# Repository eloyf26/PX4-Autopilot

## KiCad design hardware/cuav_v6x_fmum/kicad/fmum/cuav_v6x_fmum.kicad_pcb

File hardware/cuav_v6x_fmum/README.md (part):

# CUAV V6X FMUM — what the board is, and a reverse-engineered schematic

Two photos of a small green 36 × 31 mm board, silkscreened **`V6X_FMUM RC11`**, a
CUAV logo and the date code **07-17/23**. This folder identifies it, explains every
visible part, and reconstructs its schematic well enough to build a compatible
replica.

| File | What it is |
| --- | --- |
| `README.md` | this document |
| `kicad/fmum/cuav_v6x_fmum.kicad_pro` | **KiCad 8 project of the FMU module**: 4 schematic sheets + `cuav_v6x_fmum.kicad_pcb` (36 × 31.4 mm, 6 layers, placed, net-assigned, unrouted) |
| `kicad/imu/cuav_v6x_imu.kicad_pro` | **KiCad 8 project of the IMU board**: schematic + `cuav_v6x_imu.kicad_pcb` (~25 × 18 mm octagon, 4 layers, placed, unrouted) |
| `kicad/lib/` | the official KiCad 8 footprints used (fetched from the 8.0.8 library tag) and ST's pin-data XML for the STM32H743IIKx ball map |
| `parts.py` | the parts database: every component, its real package pin numbers and nets, board side and position |
| `gen_kicad.py`, `gen_pcb.py` | generators for the schematics and the two PCBs (run in this order) |
| `schematic/01…07_*.svg` | seven schematic sheets (MCU, core peripherals, power + sensors, X1, X2, IMU flex, IMU board) |
| `netlist.csv` | every MCU pin / connector pin / IMU-board pin → net → destination, machine readable |
| `gen_schematic.py` | the pin / connector tables the SVG sheets, netlist and `parts.py` are built from |
| `build_html.py` | generator for the HTML report |
| `cuav_v6x_fmum_schematic.html` | self-contained report (same content as the published artifact) |
| `photos/` | the four source photos (FMU module and IMU board), downscaled |

> **Are these the official schematics? No.** CUAV does not publish the schematic of
> the V6X modules, and the full Pixhawk FMUv6X reference schematics are available only
> to Dronecode Foundation members. Everything here is an independent reconstruction.
> Connectivity is derived from the firmware that runs on this exact hardware, so it is
> reliable; part choices for regulators and passives are engineering substitutes.

> **Provenance / confidence.** No vendor schematic of this module is public. The
> schematic below was rebuilt from three sources that describe this exact hardware:
> (1) the PX4 board support package the module runs
> (`boards/px4/fmu-v6x`, hardware type `V6X001` = "CUAV sensor set rev 1"), which
> hard-codes every MCU pin, bus, chip-select, address and power-enable;
> (2) the two public Pixhawk standards the module implements, DS-010 *Pixhawk
> Autopilot Bus* (the 100- and 50-pin connector pinouts) and DS-012 *Pixhawk
> Autopilot FMUv6X* (sensor sets, the 34-pin IMU flex pinout, mechanical drawing);
> (3) the photos, for placement, packages and markings.
> Pin-to-net connectivity is therefore high confidence. Passive values, regulator
> part numbers and a few small ICs are educated engineering choices and are
> marked as such.

---

## 1. Identification

**It is the FMU core module ("FMUM") of the CUAV Pixhawk V6X flight controller.**

The Pixhawk V6X is a modular autopilot: a *base board* (all the JST-GH connectors,
power selection, CAN/USB/Ethernet transceivers, the STM32F103 IO co-processor) and a
plug-in *FMU module* carrying the main processor, storage and part of the sensor set.
The two boards meet through the **Pixhawk Autopilot Bus (PAB)**: one 100-pin and one
50-pin Hirose DF40 connector with a 3 mm stack height. Your board is the plug-in
module. CUAV sells the V6X either complete or as this "core" alone (43 g, 36 × 31.4 mm
per the standard's mechanical drawing, which the photos match to the millimetre:
four 2.0 mm grounded mounting holes, R2.3 corners, LEDs and SD slot in the
standardised positions).

Everything on it maps to the standard's reference module drawing (DS-012 p.10,
"FMUv6X FMUM"): same FLEX connector position, same TRACE pad footprint, same
LED/SD/battery placement. CUAV re-laid the board but kept the reference architecture.

### What the photos show

**Photo 1 — MCU side (this is the *bottom* of the module; it faces the base board)**

| What you see | What it is | Confidence |
| --- | --- | --- |
| 10 × 10 mm BGA marked ARM / `STM32H7…IIK6` | **U1, STM32H743IIK6** (or H753, the crypto variant PX4 is configured for). Cortex-M7 at 480 MHz, 2 MB flash, 1 MB RAM, UFBGA176+25 package. | high |
| 100-pin fine-pitch connector, left | **X1** Hirose DF40C-100DP-0.4V — the main Pixhawk Autopilot Bus | high |
| 50-pin fine-pitch connector, right | **X2** Hirose DF40C-50DP-0.4V — Ethernet RMII + external SPI bus | high |
| 3 × 3 mm QFN, top centre | **ICM-20649** 6-axis IMU (#3), on SPI1 — the one "hard mounted" IMU of the set | high (from firmware; size matches QFN-24 3×3) |
| tiny metal-lidded part with a port hole, sitting in a U-shaped routed slot, top right | **ICP-20100** barometer (#2), on I2C2 at 0x63. The slot is stress relief: board flex would otherwise read as pressure. | high (2 × 2.5 mm metal-lid LGA is unique to a baro) |
| two small metal cans left of the MCU (`TW2…` rectangular, `A-T` square) | **Y1 16 MHz** HSE crystal (3225) and **Y2 32.768 kHz** RTC crystal | high (PX4 board.h: 16 MHz HSE, 32.768 kHz LSE) |
| small blue 1.5 mm part marked `IY2K`, right of the IMU | small passive/IC, probably an ESD/TVS array or a tiny LDO for the sensor domain | low |
| QFN + large inductor + capacitors, bottom centre | **U_REG**, the module's 5 V → 3.3 V step-down for `FMU_VDD_3V3` | medium |
| SOT-23-5 ICs and clusters of 0402 capacitors along the right edge | the four **switched sensor LDOs** (`VDD_3V3_SENSORS1…4`) with their decoupling | medium |
| `TP1` | test pad | — |
| ladders of 0402 resistors bottom right | hardware-ID resistor ladders + I²C pull-ups (1.5 kΩ, required on the module by DS-010) | medium |

**Photo 2 — SD-card side (the *top* of the module; visible when installed)**

| What you see | What it is | Confidence |
| --- | --- | --- |
| `CUAV`, `V6X_FMUM RC11`, `07-17/23`, arrow | vendor, board name (V6X **F**light **M**anagement **U**nit **M**odule), layout revision RC11, build date; the arrow is the flight direction reference for the IMUs | high |
| 34-pin connector labelled `FLEX`, left | **J3** Hirose BM20B(0.8)-34DP-0.4V, FPC to CUAV's separate, vibration-isolated **IMU board** (BMI088, ICM-42688-P, RM3100, ICP-20100 #1, calibration EEPROM). That is why the "triple-redundant IMU" is not visible here: two of the three IMUs and the compass live on the other board. | high |
| microSD push-push slot marked `molex 2011EC` | **J4** microSD, SDMMC2 4-bit, PX4 logs go here | high |
| SOIC-8, top centre | **FM25V02A** 256 kbit FRAM (SPI5) — PX4 parameter storage. FRAM is used instead of flash because it survives millions of writes and needs no erase. | high |
| 3 × 3 mm QFN marked `S50 08 07 AD307`, right of the SD slot | most likely **NXP SE050** secure element (I2C4, 0x48) — it is in the FMUv6X reference sensor set and PX4 defines its address for this board | medium |
| round metal can marked `L03`, bottom right | **B1**, RTC backup cell (rechargeable lithium coin/cylinder). Keeps the clock and backup SRAM alive without main power; exported to the base on X1-29. | high (role) / medium (exact part) |
| three 0603 LEDs bottom left | **D1 red, D2 green, D3 blue** status LEDs (PE3/PE4/PE5, active-low) | high |
| row of 8 pads + 2 large pads, bottom left | unpopulated **J1 TRACE** footprint (Cortex-M ETM trace: TRACECLK + TRACED0-3) | high |
| `BT0` pad | **BOOT0** — bridge to 3.3 V at power-up to enter the STM32 ROM (DFU) bootloader | high |
| `TP2 TP3 TP4 TP7` | test pads (nets unknown) | — |
| SOT-23 / 0603 parts around the right edge | the remaining sensor LDO and its decoupling, RTC charging diode + resistor | medium |

### Sensor set of this exact revision (from `boards/px4/fmu-v6x/init/rc.board_sensors`, branch `V6X001`)

| Sensor | Part | Bus | CS / address | DRDY | Power domain | Where |
| --- | --- | --- | --- | --- | --- | --- |
| IMU 1 | Bosch **BMI088** (accel + gyro) | SPI3 | PI4 (accel), PI8 (gyro) | PI7 (gyro INT3) | `VDD_3V3_SENSORS3` | IMU board via J3 |
| IMU 2 | TDK **ICM-42688-P** | SPI2 | PH5 | PA10 | `VDD_3V3_SENSORS2` | IMU board via J3 |
| IMU 3 | TDK **ICM-20649** | SPI1 | PI9 | PF2 | `VDD_3V3_SENSORS1` | **this module** |
| Compass | PNI **RM3100** | I2C4 | 0x20 | — | `VDD_3V3_SENSORS4` | IMU board via J3 |
| Baro 1 | TDK **ICP-20100** | I2C4 | 0x64 | — | `VDD_3V3_SENSORS4` | IMU board via J3 |
| Baro 2 | TDK **ICP-20100** | I2C2 | 0x63 | PG5 (optional) | `VDD_3V3_SENSORS2` | **this module** |
| Cal EEPROM | 24LC64 | I2C4 | 0x50 | — | `VDD_3V3_SENSORS4` | IMU board via J3 |
| Parameters | **FM25V02A** FRAM | SPI5 | PG7 | — | `FMU_VDD_3V3` | **this module** |
| Secure element | NXP **SE050** | I2C4 | 0x48 | — | `FMU_VDD_3V3` | **this module** (likely) |

### The second board: `V6X IMU RC10` (2022-09-20)

The octagonal board on the other end of the FLEX cable is CUAV's **IMU board**. It sits
in an elastomer isolation mount (the two half-round notches and the four M1-M4 ground
pads are the mount interface), which is why it is a separate PCB at all: the inertial
sensors ride on a damped mass, while the processor board is bolted rigidly to the base.
It contains no regulators; all its power arrives over the flex.

| What you see | What it is | Confidence |
| --- | --- | --- |
| rectangular LGA, top left, sensor side | **Bosch BMI088** accel + gyro (IMU 1, SPI3) | high (package 3 × 4.5 mm, firmware) |
| small 3-row-marked LGA below it | **TDK ICM-42688-P** (IMU 2, SPI2) | high |
| 4 × 4 mm QFN, centre right | **PNI MagI2C**, the RM3100 compass controller (I2C4, 0x20) | high |
| two flat black bars marked `PNI`, one horizontal one vertical | **PNI Sen-XY-f** sense coils for the X and Y magnetic axes (mounted at 90°) | high |
| black cube below the QFN | **PNI Sen-Z-f** coil, Z axis | high |
| metal lid with port hole, bottom left | **TDK ICP-20100** barometer #1 (I2C4, 0x64) | high |
| white arrow | flight-direction reference for the IMU axes | high |
| flex side: 34-pin 0.4 mm connector `FLEX` | mating half of the FMUM's J3 (BM20 series); an FPC jumper links the two | high |
| flex side: SOIC-8 | **24LC64** calibration EEPROM (I2C4, 0x50; PX4 `imu_eeprom`: cal data, MFT revision, ID) | high |
| flex side: four large resistors marked `4700` | **470 Ω heater resistors**, paralleled (117 Ω across 5 V ≈ 0.21 W) | high |
| flex side: SOT-23 marked `3400` next to a resistor silkscreen symbol | **N-MOSFET (AO3400 class)**, low-side switch for the heater, gate on the `HEATER` line | high |
| remaining 0402/0603 parts | decoupling, gate pull-down | — |

Sheet `07_imu_board.svg` (and KiCad sheet 5) draws it. Because the flex pinout is fixed by
the standard, the IMU board and the FMU module are individually replaceable; the
sensor rotations PX4 applies (`-R 4` BMI088, `-R 6` ICM-42688-P, `-R 14` ICM-20649) encode how
each chip is oriented relative to the arrow.

---

## 2. How the module works (architecture)

```
             base board                        ┃  FMU module (this board)                         ┃  IMU board (flex)
                                               ┃                                                   ┃
  power path selector ── VDD_5V_IN ────────────╋──► U_REG 3.3 V ──► FMU_VDD_3V3 ──► U1 STM32H7     ┃
  (2 bricks + USB)      X1-49/51/53/55         ┃      │                     ├──► FM25V02A FRAM (SPI5) ┃
                                               ┃      │                     ├──► SE050 (I2C4)        ┃
                                               ┃      │                     ├──► microSD (SDMMC2, switched by PC13)
                                               ┃      ├──► LDO1 (PI11) ──► ICM-20649  (SPI1)        ┃
                                               ┃      ├──► LDO2 (PF4)  ──► ICP-20100 #2 (I2C2) ─────╋──► ICM-42688-P (SPI2)
                                               ┃      ├──► LDO3 (PE7)  ────────────────────────────╋──► BMI088 (SPI3)
                                               ┃      └──► LDO4 (PG8)  ────────────────────────────╋──► RM3100, ICP-20100 #1, EEPROM (I2C4)
  UARTs, CAN, USB, PWM, I2C1-3, ADC, IDs ◄─────╋── X1 (100 pins) ── U1 GPIO/peripherals             ┃      HEATER (PB10) ◄── J3-30
  LAN8742A PHY (RMII), payload SPI6 ◄──────────╋── X2 (50 pins)                                    ┃
```

Key ideas worth understanding before you copy it:

* **One supply in, everything else generated locally.** Only `VDD_5V_IN` enters (four
  pins for current). A step-down makes `FMU_VDD_3V3` for the MCU and memories, and that
  rail is *exported* on X1-84/86 so the base can run its own small logic from it.
* **Four independent sensor power domains.** Each IMU/compass group has its own 3.3 V
  LDO with an MCU-controlled enable and a 1:2 resistor divider read by the ADC. PX4 can
  power-cycle a misbehaving sensor domain without touching the others and can detect a
  sagging rail. This is the "three redundancy domains" design of FMUv6X.
* **Separate buses per IMU.** SPI1, SPI2, SPI3 each carry exactly one IMU (plus a data-ready
  interrupt line), so a hung device cannot block the others. I2C4 is the internal
  sensor I²C (compass, baro 1, EEPROM, secure element). I2C1/2/3 go out to the base for
  GPS/compass pucks and power monitors; baro 2 rides on I2C2 locally.
* **Storage:** FRAM for parameters (byte-writable, non-volatile), microSD for logs, backup
  SRAM + RTC kept alive by B1.
* **Hardware identification without firmware changes.** At boot PG0 drives 3.3 V into two
  resistor ladders; ADC3 reads the divider voltages. PH4 reads the *module* ladder
  (24.9 k / 442 k → ID 1 → "CUAV sensor set rev 1"), PH3 reads the *base board* ladder via
  X1-27. PX4 then starts exactly the right drivers with the right axis rotations.
* **Everything analog-ish that touches the outside world stays on the base**: USB/CAN
  transceivers, RS-232-level shifters, PHY magnetics, power switching, ESD. Only 3.3 V
  logic crosses X1/X2. That is what makes the module small and reusable.

---

## 3. Schematic sheets

### KiCad — two projects, two PCBs

```
kicad/fmum/cuav_v6x_fmum.kicad_pro     FMU module   (schematic, 4 sheets + PCB)
kicad/imu/cuav_v6x_imu.kicad_pro       IMU board    (schematic + PCB)
```

Open either `.kicad_pro` in KiCad 8 or newer. Everything is self-contained: symbols are
embedded in the sheets and footprints in the boards, so no library setup is needed.

**What the PCBs contain, and how much to trust each part**

| Item | Status |
| --- | --- |
| FMUM outline 36.0 × 31.4 mm, R2.3 corners, four ∅2.0 grounded holes at 2.3 mm from the edges | from the Pixhawk DS-010 drawing — exact |
| X1 / X2 positions (4.1 and 33.0 mm from the left edge in the base-side view, centred 14.5 mm from the bottom edge), pin 1 at the bottom, odd pins on the left in that view | from DS-010 — exact position; pin-1 corner follows the drawing |
| LED positions (blue 6.70, green 8.30, red 9.85 mm from the left, 2.3 mm from the bottom) | from DS-010 — exact |
| Baro stress-relief slot, IMU flex connector, microSD, FRAM, crystals, RTC cell, regulators, passives | positions read off the photos, about ±0.5 mm |
| Every pad's net (670 pads on the FMUM, 171 on the IMU board) | from the firmware pin map and the datasheets — reliable |
| STM32H743IIK6 footprint: 201 balls on a 0.65 mm grid, ball names from ST's own pin data, 0.30 mm pads | exact |
| Footprints for SOIC-8, QFN-20/24, LGA-14, SOT-23/-223, 0402/0603/0805, crystals, LEDs, microSD | official KiCad 8 library files (`kicad/lib/`) |
| Generated footprints: DF40 100/50-pin, BM20 34-pin, BMI088 LGA-16, ICP-20100 LGA-10, MagI2C MLF-28, PNI coils, RTC cell, test/trace pads | pin order from the datasheets; pad **geometry approximated** — compare with the Hirose / PNI / Bosch / TDK drawings before ordering boards |
| IMU board outline (25 × 18 mm octagon, 4.8 / 4.0 mm chamfers, ∅3 mm notches, ∅2.2 holes) | estimated from the photos using the coils and connector as scale |
| Copper routing, inner-layer planes, vias | **not included** — a 6-layer BGA design cannot be recovered from photographs. The ratsnest is complete; route it yourself |

Substitute parts (the replica choice, not the original): U2 3.3 V regulator (an LDO in SOT-223
stands in for CUAV's switching regulator), U3–U6 sensor LDOs (TLV75533 pinout: IN, GND, EN, NC, OUT),
U7 microSD load switch (check the pinout of the part you buy), BT1 (Seiko MS621FE footprint).
U11 (SE050 secure element) is placed with its pads deliberately **unassigned** because its pinout
could not be verified; PX4 runs without it.

**Working with it**

* Pin numbers in the schematic symbols are the real package pins, so *Update PCB from Schematic*
  round-trips cleanly. Click a global label and press ` to highlight a net across sheets.
* Front side of the FMUM PCB = SD-card side; the MCU, bus connectors, IMU 3 and barometer sit on the
  back (B.Cu), which is what plugs toward the base board.
* Set the FMUM stackup to 6 layers (F.Cu, In1–In4, B.Cu are defined); use In1/In4 as ground and
  power planes next to the outer layers, 0.1 mm/0.1 mm rules and 0.2 mm vias for the BGA escape.
* ERC/DRC will flag the intentionally open pins (X2 spares, SE050, unused INT pins) and the
  unrouted nets.
* Regenerate after editing `parts.py`: `python3 gen_kicad.py && python3 gen_pcb.py`.

### SVG sheets

Open the SVGs in `schematic/` (any browser or Inkscape). Net labels
follow the Pixhawk standard names so they line up with the published base-board
examples.

| Sheet | Content |
| --- | --- |
| `01_mcu_u1.svg` | U1 with every used pin: peripheral function inside, net outside, destination in the margin |
| `02_core_peripherals.svg` | FRAM, SE050, microSD + load switch, crystals, RTC cell, LEDs, USB, HW-ID ladder, BOOT0/NRST/TRACE |
| `03_power_and_sensors.svg` | 3.3 V step-down, four sensor LDOs with dividers, ICM-20649, ICP-20100 #2, heater line, I²C pull-ups |
| `04_x1_pab_100pin.svg` | X1 pin-by-pin with the MCU pin on each signal |
| `05_x2_pab_50pin.svg` | X2 pin-by-pin (RMII, SPI6, spares) |
| `06_j3_imu_flex_34pin.svg` | J3 IMU flex pin-by-pin |
| `07_imu_board.svg` | the IMU board: BMI088, ICM-42688-P, RM3100 (MagI2C + 3 coils), ICP-20100 #1, 24LC64, heater |

### Full MCU pin map (as used by PX4 on this module)

Column "goes to" uses the same vocabulary as the sheets: `X1-nn`, `X2-nn`, `J3-nn`, or an on-module part.

| Pin | Function | Net | Goes to |
| --- | --- | --- | --- |
| PA0 | ADC1_INP16 | SCALED_VDD_3V3_SENSORS1 | divider on sensor rail 1 |
| PA1 | ETH_REF_CLK | ETH_REF_CLK | X2-3 |
| PA2 | ETH_MDIO | ETH_MDIO | X2-2 |
| PA3 | USART2_RX | USART2_RX_TELEM3 | X1-42 |
| PA4 | ADC12_INP18 | SCALED_VDD_3V3_SENSORS2 | divider on sensor rail 2 |
| PA5 | SPI1_SCK | SPI1_SCK_SENSOR1 | ICM-20649 SCLK |
| PA6 | SPI6_MISO | SPI6_MISO_EXTERNAL1 | X2-31 |
| PA7 | ETH_CRS_DV | ETH_CRS_DV | X2-7 |
| PA8 | I2C3_SCL | I2C3_SCL_BASE | X1-10 |
| PA9 | OTG_FS_VBUS | VBUS_SENSE | X1-80 |
| PA10 | GPIO/EXTI | SPI2_DRDY2_IMU2_INT2 | J3-31 |
| PA11 | OTG_FS_DM | USB_D_N | X1-78 |
| PA12 | OTG_FS_DP | USB_D_P | X1-76 |
| PA13 | SWDIO | FMU_SWDIO | X1-75 |
| PA14 | SWCLK | FMU_SWCLK | X1-77 |
| PA15 | GPIO | SPI6_nCS2_EXTERNAL1 | X2-43 |
| PB0 | ADC12_INP9 | SCALED_VDD_3V3_SENSORS3 | divider on sensor rail 3 |
| PB1 | ADC12_INP5 | SCALED_V5 | divider on VDD_5V_IN |
| PB2 | SPI3_MOSI | SPI3_MOSI_SENSOR3 | J3-14 |
| PB3 | SPI6_SCK / SWO | SPI6_SCK_EXTERNAL1 | X2-35 |
| PB4 | SDMMC2_D3 | SD_D3 | microSD |
| PB5 | SPI1_MOSI | SPI1_MOSI_SENSOR1 | ICM-20649 SDI |
| PB6 | USART1_TX | USART1_TX_GPS1 | X1-36 |
| PB7 | USART1_RX | USART1_RX_GPS1 | X1-34 |
| PB8 | I2C1_SCL | I2C1_SCL_BASE | X1-18 |
| PB9 | I2C1_SDA | I2C1_SDA_BASE | X1-16 |
| PB10 | GPIO (TIM2_CH3) | HEATER | J3-30 |
| PB11 | ETH_TX_EN | ETH_TX_EN | X2-27 |
| PB12 | FDCAN2_RX | CAN2_RX | X1-59 |
| PB13 | FDCAN2_TX | CAN2_TX | X1-57 |
| PB14 | SDMMC2_D0 | SD_D0 | microSD |
| PB15 | SDMMC2_D1 | SD_D1 | microSD |
| PC0 | GPIO/EXTI | NFC_GPIO | X2-48 |
| PC1 | ETH_MDC | ETH_MDC | X2-4 |
| PC2 | ADC3_INP12 | ADC1_6V6 | X1-90 |
| PC3 | ADC3_INP13 | ADC1_3V3 | X1-92 |
| PC4 | ETH_RXD0 | ETH_RXD0 | X2-11 |
| PC5 | ETH_RXD1 | ETH_RXD1 | X2-15 |
| PC6 | USART6_TX | USART6_TX_TO_IO | X1-72 |
| PC7 | USART6_RX | USART6_RX_FROM_IO_RC | X1-70 |
| PC8 | UART5_RTS | UART5_RTS_TELEM2 | X1-58 |
| PC9 | UART5_CTS | UART5_CTS_TELEM2 | X1-60 |
| PC10 | SPI3_SCK | SPI3_SCK_SENSOR3 | J3-10 |
| PC11 | SPI3_MISO | SPI3_MISO_SENSOR3 | J3-12 |
| PC12 | UART5_TX | UART5_TX_TELEM2 | X1-52 |
| PC13 | GPIO | VDD_3V3_SD_CARD_EN | SD load switch |
| PC14/PC15 | OSC32 | 32 kHz crystal | Y2 |
| PD0 | FDCAN1_RX | CAN1_RX | X1-65 |
| PD1 | FDCAN1_TX | CAN1_TX | X1-63 |
| PD2 | UART5_RX | UART5_RX_TELEM2 | X1-54 |
| PD3 | USART2_CTS | USART2_CTS_TELEM3 | X1-48 |
| PD4 | USART2_RTS | USART2_RTS_TELEM3 | X1-46 |
| PD5 | USART2_TX | USART2_TX_TELEM3 | X1-40 |
| PD6 | SDMMC2_CK | SD_CLK | microSD |
| PD7 | SDMMC2_CMD | SD_CMD | microSD |
| PD8 | USART3_TX | USART3_TX_DEBUG | X1-69 |
| PD9 | USART3_RX | USART3_RX_DEBUG | X1-71 |
| PD10 | GPIO | FMU_nSAFETY_SWITCH_LED_OUT | X1-23 |
| PD11 | GPIO | SPI6_DRDY1_EXTERNAL1 | X2-47 |
| PD12 | GPIO | SPI6_DRDY2_EXTERNAL1 | X2-45 |
| PD13 | TIM4_CH2 | FMU_CH5 | X1-7 |
| PD14 | TIM4_CH3 | FMU_CH6 | X1-5 |
| PD15 | GPIO | spare | n.c. |
| PE0 | UART8_RX | UART8_RX_GPS2 | X1-30 |
| PE1 | UART8_TX | UART8_TX_GPS2 | X1-28 |
| PE2 | TRACECLK | TRACECLK | J1 pad 1 |
| PE3 | GPIO, open drain | nLED_RED | D1 (+ J1 pad 3) |
| PE4 | GPIO, open drain | nLED_GREEN | D2 (+ J1 pad 5) |
| PE5 | GPIO, open drain | nLED_BLUE | D3 (+ J1 pad 7) |
| PE6 | GPIO | nARMED | X1-85 (+ J1 pad 8) |
| PE7 | GPIO | VDD_3V3_SENSORS3_EN | LDO3 EN |
| PE8 | UART7_TX | UART7_TX_TELEM1 | X1-64 |
| PE9 | GPIO | SPIX_SYNC | X2-49 |
| PE10 | UART7_CTS | UART7_CTS_TELEM1 | X1-24 |
| PE11 | TIM1_CH2 capture | FMU_CAP1 | X1-97 |
| PE15 | GPIO | VDD_5V_PERIPH_nOC | X1-37 |
| PF0 | I2C2_SDA | I2C2_SDA_BASE | X1-12 + ICP-20100 #2 |
| PF1 | I2C2_SCL | I2C2_SCL_BASE | X1-14 + ICP-20100 #2 |
| PF2 | GPIO/EXTI | SPI1_DRDY1_IMU3_INT1 | ICM-20649 INT1 |
| PF4 | GPIO | VDD_3V3_SENSORS2_EN | LDO2 EN |
| PF5 | GPIO, pull-up | FMU_SAFETY_SWITCH_IN | X1-21 |
| PF6 | UART7_RX | UART7_RX_TELEM1 | X1-66 |
| PF7 | SPI5_SCK | SPI5_SCK_FRAM | FRAM SCK |
| PF8 | UART7_RTS | UART7_RTS_TELEM1 | X1-22 |
| PF9 | TIM14_CH1 | BUZZER_1 | X1-4 |
| PF10 | GPIO | SPI6_nRESET_EXTERNAL1 | X2-39 |
| PF11 | SPI5_MOSI | SPI5_MOSI_FRAM | FRAM SI |
| PF12 | ADC1_INP6 | SCALED_VDD_3V3_SENSORS4 | divider on sensor rail 4 |
| PF13 | GPIO | VDD_5V_HIPOWER_nOC | X1-83 |
| PF14 | I2C4_SCL | I2C4_SCL_FMU | J3-7 + SE050 |
| PF15 | I2C4_SDA | I2C4_SDA_FMU | J3-5 + SE050 |
| PG0 | GPIO | HW_VER_REV_DRIVE | X1-25 + module ID ladder |
| PG1 | GPIO, pull-up | nPOWER_IN_A | X1-89 |
| PG2 | GPIO, pull-up | nPOWER_IN_B | X1-91 |
| PG3 | GPIO, pull-up | nPOWER_IN_C | X1-93 |
| PG4 | GPIO | VDD_5V_PERIPH_nEN | X1-35 |
| PG5 | GPIO/EXTI | I2C2_DRDY1_BARO2 | ICP-20100 #2 INT (optional) |
| PG6 | GPIO, pull-up | PG6 | X2-44 |
| PG7 | GPIO | SPI5_nCS1_FRAM | FRAM nCS |
| PG8 | GPIO | VDD_3V3_SENSORS4_EN | LDO4 EN |
| PG9 | SPI1_MISO | SPI1_MISO_SENSOR1 | ICM-20649 SDO |
| PG10 | GPIO | VDD_5V_HIPOWER_nEN | X1-81 |
| PG11 | SDMMC2_D2 | SD_D2 | microSD |
| PG12 | ETH_TXD1 | ETH_TXD1 | X2-23 |
| PG13 | ETH_TXD0 | ETH_TXD0 | X2-19 |
| PG14 | SPI6_MOSI | SPI6_MOSI_EXTERNAL1 | X2-33 |
| PG15 | GPIO | ETH_POWER_EN | X2-6 |
| PH0/PH1 | OSC | 16 MHz crystal | Y1 |
| PH2 | GPIO | VDD_3V3_SPEKTRUM_POWER_EN | X1-33 |
| PH3 | ADC3_INP14 | HW_VER_SENSE | X1-27 (base ID ladder) |
| PH4 | ADC3_INP15 | HW_REV_SENSE | module ID ladder |
| PH5 | GPIO | SPI2_nCS1_IMU2 | J3-33 |
| PH6 | TIM12_CH1 | FMU_CH7 | X1-3 |
| PH7 | SPI5_MISO | SPI5_MISO_FRAM | FRAM SO |
| PH8 | I2C3_SDA | I2C3_SDA_BASE | X1-8 |
| PH9 | TIM12_CH2 | FMU_CH8 | X1-1 |
| PH10 | TIM5_CH1 | FMU_CH4 | X1-11 |
| PH11 | TIM5_CH2 | FMU_CH3 | X1-13 (+ X2-50) |
| PH12 | TIM5_CH3 | FMU_CH2 | X1-15 |
| PH13 | UART4_TX | UART4_TX | X1-98 |
| PH14 | UART4_RX | UART4_RX | X1-96 |
| PI0 | TIM5_CH4 | FMU_CH1 | X1-17 |
| PI1 | SPI2_SCK | SPI2_SCK_SENSOR2 | J3-20 |
| PI2 | SPI2_MISO | SPI2_MISO_SENSOR2 | J3-22 |
| PI3 | SPI2_MOSI | SPI2_MOSI_SENSOR2 | J3-24 |
| PI4 | GPIO | SPI3_nCS1_BMI088_ACCEL | J3-2 |
| PI5 | TIM8_CH1 capture | FMU_PPM_INPUT | X1-39 |
| PI6 | GPIO | SPI3_DRDY1_BMI088_INT1 | n.c. (not on flex) |
| PI7 | GPIO/EXTI | SPI3_DRDY2_BMI088_INT3_GYRO | J3-3 |
| PI8 | GPIO | SPI3_nCS2_BMI088_GYRO | J3-4 |
| PI9 | GPIO | SPI1_nCS1_IMU3 | ICM-20649 nCS |
| PI10 | GPIO | SPI6_nCS1_EXTERNAL1 | X2-41 |
| PI11 | GPIO | VDD_3V3_SENSORS1_EN | LDO1 EN |
| NRST | reset | FMU_nRST | X1-87 |
| BOOT0 | boot | BOOT0 | BT0 pad, 10 k to GND |
| VBAT | backup | V_RTC_BAT | B1 + X1-29 |

Serial ports as PX4 names them: USART1 = GPS1, USART2 = TELEM3, USART3 = debug
console, UART4 = "UART4/I2C3" port, UART5 = TELEM2, USART6 = PX4IO link and RC input
(1.5 Mbit/s), UART7 = TELEM1, UART8 = GPS2.

### X1 — 100-pin Pixhawk Autopilot Bus (module part: Hirose DF40C-100DP-0.4V(51))

Odd pins on one row, even on the other. `GND` pins: 2 6 9 19 20 26 31 32 38 41 43 44 45 47 50 56 61 62 67 68 73 74 79 82 88 94 95 99 100.

| Pin | Net | Pin | Net |
| --- | --- | --- | --- |
| 1 | FMU_CH8 (PH9) | 4 | BUZZER_1 (PF9) |
| 3 | FMU_CH7 (PH6) | 8 | I2C3_SDA (PH8) |
| 5 | FMU_CH6 (PD14) | 10 | I2C3_SCL (PA8) |
| 7 | FMU_CH5 (PD13) | 12 | I2C2_SDA (PF0) |
| 11 | FMU_CH4 (PH10) | 14 | I2C2_SCL (PF1) |
| 13 | FMU_CH3 (PH11) | 16 | I2C1_SDA (PB9) |
| 15 | FMU_CH2 (PH12) | 18 | I2C1_SCL (PB8) |
| 17 | FMU_CH1 (PI0) | 22 | UART7_RTS_TELEM1 (PF8) |
| 21 | FMU_SAFETY_SWITCH_IN (PF5) | 24 | UART7_CTS_TELEM1 (PE10) |
| 23 | FMU_nSAFETY_SWITCH_LED_OUT (PD10) | 28 | UART8_TX_GPS2 (PE1) |
| 25 | HW_VER_REV_DRIVE (PG0) | 30 | UART8_RX_GPS2 (PE0) |
| 27 | HW_VER_SENSE (PH3) | 34 | USART1_RX_GPS1 (PB7) |
| 29 | V_RTC_BAT (VBAT, B1) | 36 | USART1_TX_GPS1 (PB6) |
| 33 | VDD_3V3_SPEKTRUM_POWER_EN (PH2) | 40 | USART2_TX_TELEM3 (PD5) |
| 35 | VDD_5V_PERIPH_nEN (PG4) | 42 | USART2_RX_TELEM3 (PA3) |
| 37 | VDD_5V_PERIPH_nOC (PE15) | 46 | USART2_RTS_TELEM3 (PD4) |
| 39 | FMU_PPM_INPUT (PI5) | 48 | USART2_CTS_TELEM3 (PD3) |
| 49 51 53 55 | **VDD_5V_IN** (supply in) | 52 | UART5_TX_TELEM2 (PC12) |
| 57 | CAN2_TX (PB13) | 54 | UART5_RX_TELEM2 (PD2) |
| 59 | CAN2_RX (PB12) | 58 | UART5_RTS_TELEM2 (PC8) |
| 63 | CAN1_TX (PD1) | 60 | UART5_CTS_TELEM2 (PC9) |
| 65 | CAN1_RX (PD0) | 64 | UART7_TX_TELEM1 (PE8) |
| 69 | USART3_TX_DEBUG (PD8) | 66 | UART7_RX_TELEM1 (PF6) |
| 71 | USART3_RX_DEBUG (PD9) | 70 | USART6_RX_FROM_IO / RC (PC7) |
| 75 | FMU_SWDIO (PA13) | 72 | USART6_TX_TO_IO (PC6) |
| 77 | FMU_SWCLK (PA14) | 76 | USB_D_P (PA12) |
| 81 | VDD_5V_HIPOWER_nEN (PG10) | 78 | USB_D_N (PA11) |
| 83 | VDD_5V_HIPOWER_nOC (PF13) | 80 | VBUS_SENSE (PA9) |
| 85 | nARMED (PE6) | 84, 86 | **FMU_VDD_3V3** (3.3 V out) |
| 87 | FMU_nRST (NRST) | 90 | ADC1_6V6 (PC2) |
| 89 | nPOWER_IN_A (PG1) | 92 | ADC1_3V3 (PC3) |
| 91 | nPOWER_IN_B (PG2) | 96 | UART4_RX (PH14) |
| 93 | nPOWER_IN_C (PG3) | 98 | UART4_TX (PH13) |
| 97 | FMU_CAP1 (PE11) | | |

### X2 — 50-pin Pixhawk Autopilot Bus (module part: Hirose DF40C-50DP-0.4V(51))

`GND`: 1 5 8 9 13 14 17 21 24 25 29 34 37 46. Connected signals: 2 ETH_MDIO (PA2) · 3 ETH_REF_CLK (PA1) · 4 ETH_MDC (PC1) · 6 ETH_POWER_EN (PG15) · 7 ETH_CRS_DV (PA7) · 11 ETH_RXD0 (PC4) · 15 ETH_RXD1 (PC5) · 19 ETH_TXD0 (PG13) · 23 ETH_TXD1 (PG12) · 27 ETH_TX_EN (PB11) · 31 SPI6_MISO (PA6) · 33 SPI6_MOSI (PG14) · 35 SPI6_SCK/SWO (PB3) · 39 SPI6_nRESET (PF10) · 41 SPI6_nCS1 (PI10) · 43 SPI6_nCS2 (PA15) · 44 PG6 · 45 SPI6_DRDY2 (PD12) · 47 SPI6_DRDY1 (PD11) · 48 NFC_GPIO (PC0) · 49 SPIX_SYNC (PE9) · 50 PH11.
Defined by the standard but **not connected** on an FMUv6X module: 10 ETH_RX_ER, 12 ETH_PHY_nINT, 16/18/20/22 FMU_CH9-12, 26/28/30/32/36/38 SPARE, 40/42 CAN3.

### J3 — 34-pin IMU flex (module part: Hirose BM20B(0.8)-34DP-0.4V(53))

| Pin | Net | Pin | Net |
| --- | --- | --- | --- |
| 1 | GND | 2 | SPI3_nCS1_BMI088_ACCEL (PI4) |
| 3 | SPI3_DRDY2_BMI088_INT3_GYRO (PI7) | 4 | SPI3_nCS2_BMI088_GYRO (PI8) |
| 5 | I2C4_SDA (PF15) | 6 | VDD_3V3_SENSORS3 |
| 7 | I2C4_SCL (PF14) | 8 | GND |
| 9 | GND | 10 | SPI3_SCK (PC10) |
| 11 | GND | 12 | SPI3_MISO (PC11) |
| 13 | GND | 14 | SPI3_MOSI (PB2) |
| 15 | GND | 16 | VDD_3V3_SENSORS4 |
| 17 | GND | 18 | GND |
| 19 | GND | 20 | SPI2_SCK (PI1) |
| 21 | GND | 22 | SPI2_MISO (PI2) |
| 23 | GND | 24 | SPI2_MOSI (PI3) |
| 25 | GND | 26 | GND |
| 27 | GND | 28 | VDD_5V_IN |
| 29 | GND | 30 | HEATER (PB10) |
| 31 | SPI2_DRDY2_IMU2_INT2 (PA10) | 32 | VDD_3V3_SENSORS2 |
| 33 | SPI2_nCS1_IMU2 (PH5) | 34 | GND |

---

## 4. Bill of materials for a replica

Exact-match parts are marked ✔ (identified from photo + firmware). Others are
functional substitutes any designer would pick; the original is likely different but
electrically equivalent.

| Ref | Part | Package | Notes |
| --- | --- | --- | --- |
| U1 ✔ | STM32H743IIK6 (or STM32H753IIK6) | UFBGA176+25, 0.65 mm | needs 4-6 layer PCB with 0.3 mm vias to route |
| X1 ✔ | Hirose DF40C-100DP-0.4V(51) | 0.4 mm, 3 mm stack | base side: DF40HC(3.0)-100DS-0.4V(58) |
| X2 ✔ | Hirose DF40C-50DP-0.4V(51) | | base side: DF40HC(3.0)-50DS-0.4V(51) |
| J3 ✔ | Hirose BM20B(0.8)-34DP-0.4V(53) | 0.4 mm | to IMU board FPC |
| J4 ✔ | Molex 5031821852 microSD push-push | | any hinged/push microSD works |
| U_FRAM ✔ | Cypress/Infineon FM25V02A-G | SOIC-8 | 256 kbit, SPI up to 40 MHz |
| U_SE | NXP SE050C1HQ1/Z01SC | HX2QFN-20 | optional; PX4 boots without it |
| U_IMU3 ✔ | TDK InvenSense ICM-20649 | QFN-24 3×3 | SPI mode 3 |
| U_BARO2 ✔ | TDK InvenSense ICP-20100 | LGA-10 2×2.5 | put it in a routed slot island |
| U_REG | 3.3 V buck, 1 A (e.g. TI TPS62A01, TPS563201 for a first prototype) | QFN/SOT | + 2.2 µH inductor, 2×10 µF in, 22 µF out |
| U_LDO1-4 | 3.3 V LDO 300 mA with EN (e.g. TLV75533PDBV) | SOT-23-5 | 1 µF in/out each; EN from PI11/PF4/PE7/PG8 |
| Q_SD | load switch (e.g. TPS22918) or P-MOSFET + pull-up | SOT-23-6 | EN from PC13 |
| Y1 ✔ | 16.000 MHz crystal, CL 8-10 pF | 3225 | 2×10 pF |
| Y2 ✔ | 32.768 kHz crystal, CL 6-7 pF | 3215/2012 | 2×6.8 pF |
| B1 | rechargeable Li cell 3 V (Seiko MS621FE) or 0.1 F supercap | | charge via BAT54 + 1 kΩ from 3.3 V |
| D1-3 ✔ | red / green / blue LEDs | 0603 | 470 Ω-1 kΩ series |
| R-ID | 24.9 kΩ + 442 kΩ (module ID 1) | 0402 | 1 % |
| R-pullups | 1.5 kΩ ×8 (I2C1-4 SCL/SDA) | 0402 | to FMU_VDD_3V3 |
| R-div | 10 kΩ ×10 (5 rails, 1:2) | 0402 | |
| C | 100 nF per supply pin (≈ 20), 2×2.2 µF VCAP, 4.7 µF bulk ×3 | 0402/0603 | |
| ferrite | on VDDA/VREF+ | 0603 | |

---

## 5. Learning-project advice (how to actually replicate this)

The module is a serious 6-layer, 0.4 mm-pitch, BGA design. Copying it 1:1 is a
poor *first* board. A path that keeps the same electronics but grows with your skill:

1. **Stage 1 — same brain, big pins.** Put an STM32H743**VIT6** (LQFP-100) or ZIT6 (LQFP-144)
   on a 2-layer board with the FRAM, microSD, crystals, LEDs, USB and an SWD header.
   Keep the exact pin functions from the table above wherever the LQFP exposes them
   (most of ports A-E are there). Flash the PX4 `px4_fmu-v6x` firmware unchanged only if
   you keep the BGA pinout; otherwise create your own board directory in
   `boards/<you>/…` copied from `boards/px4/fmu-v6x` and edit `board.h` /
   `board_config.h` / `spi.cpp` / `timer_config.cpp` to your pins. That is exactly the
   procedure the tables in this document were derived from, in reverse.
2. **Stage 2 — one sensor domain.** Add one LDO with enable, one ICM-20649 (or the more
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
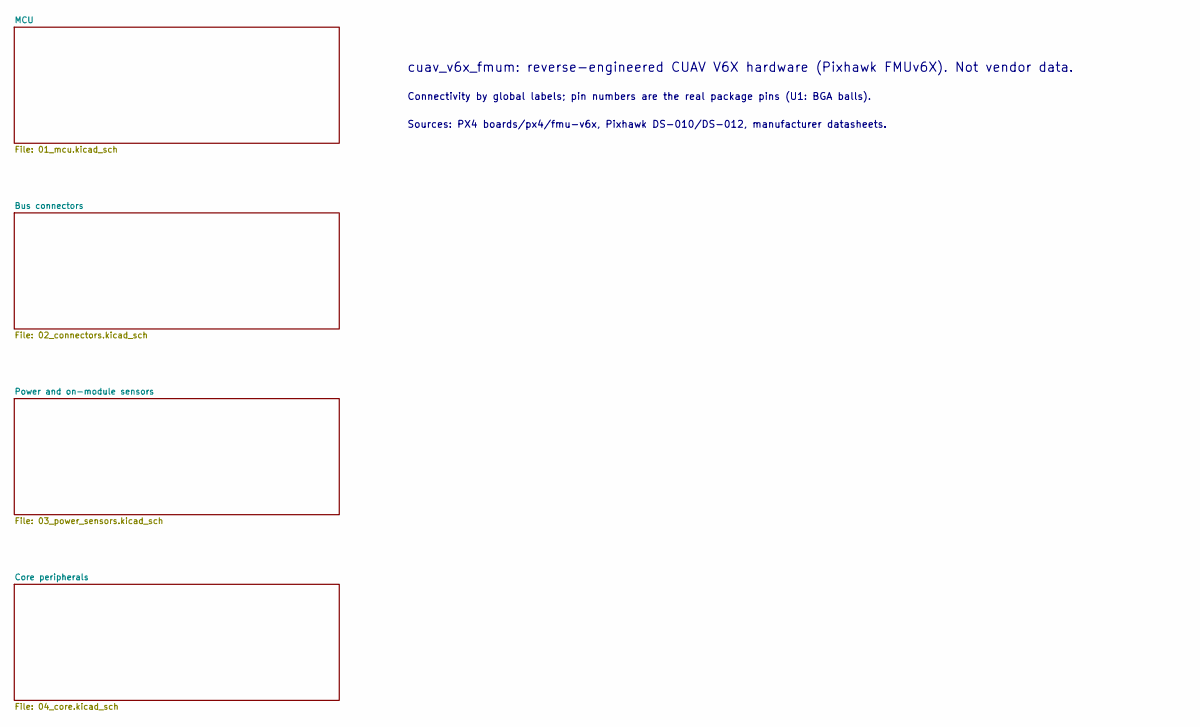
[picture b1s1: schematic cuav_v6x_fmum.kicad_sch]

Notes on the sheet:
cuav_v6x_fmum: reverse-engineered CUAV V6X hardware (Pixhawk FMUv6X). Not vendor data.
Connectivity by global labels; pin numbers are the real package pins (U1: BGA balls).
Sources: PX4 boards/px4/fmu-v6x, Pixhawk DS-010/DS-012, manufacturer datasheets.

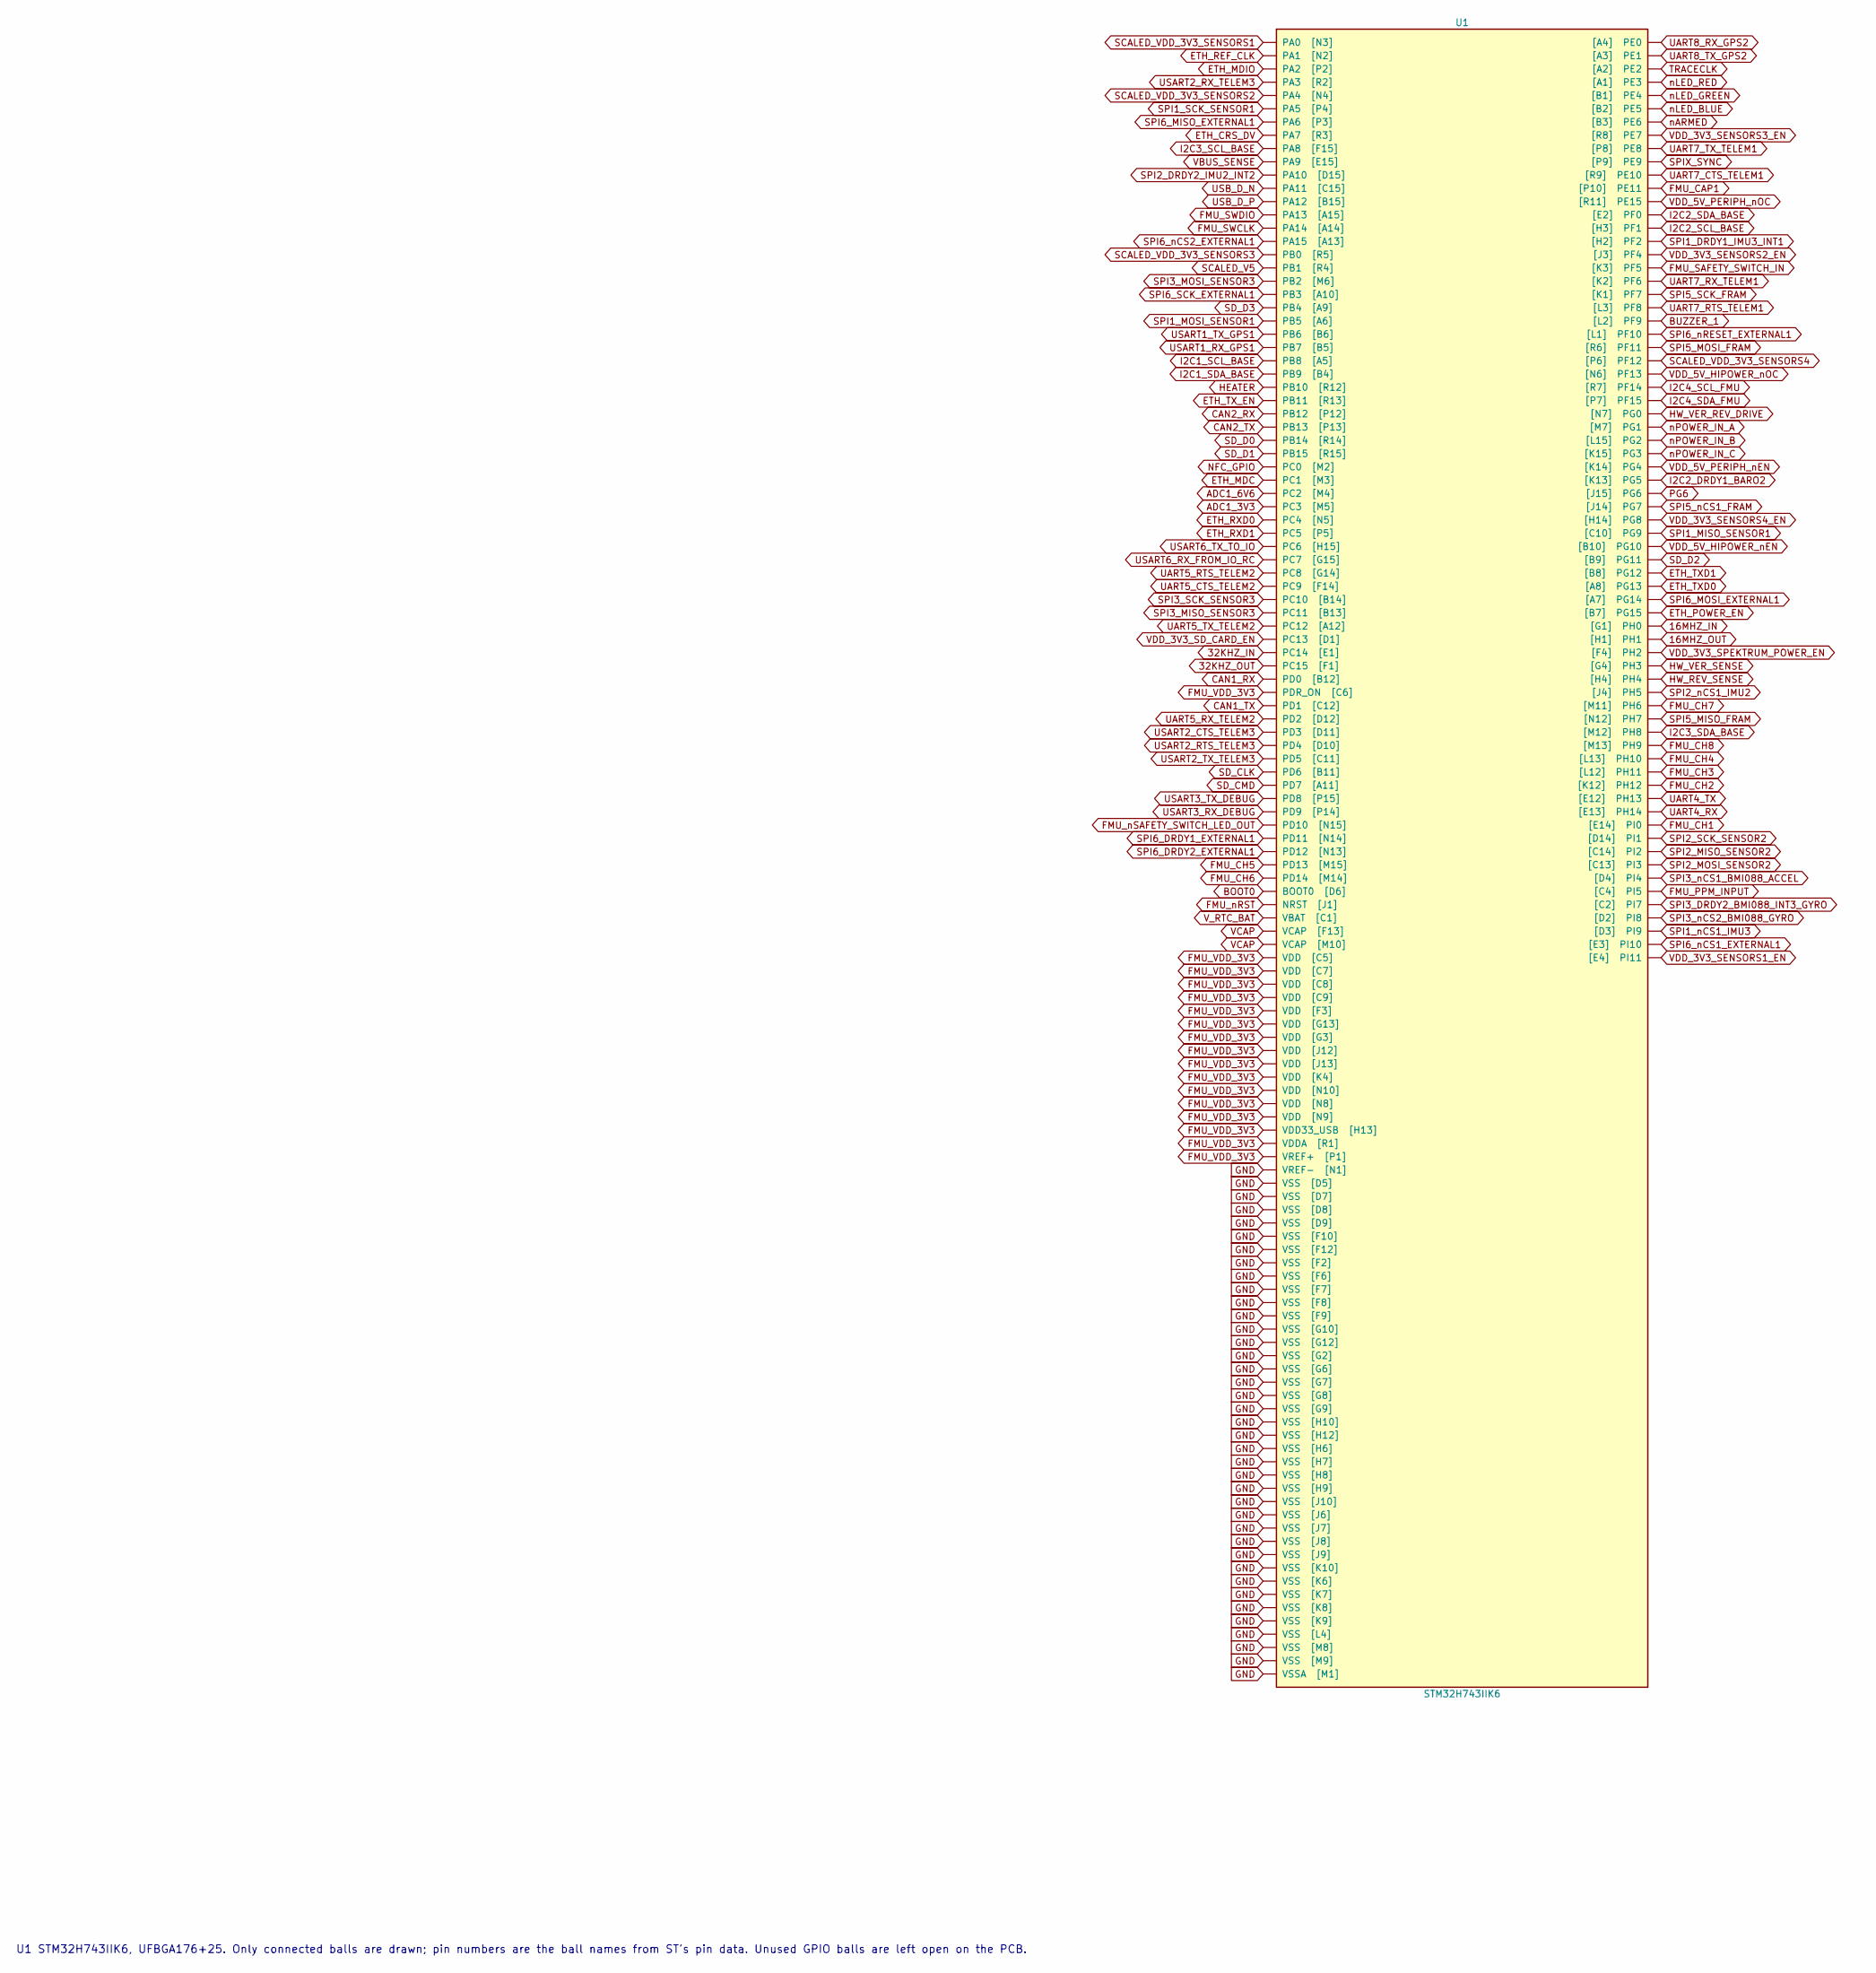
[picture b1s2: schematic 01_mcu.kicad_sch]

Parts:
U1: STM32H743IIK6; ST_UFBGA-176+25_10x10mm_Layout15x15_P0.65mm

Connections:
16MHZ_IN: U1.G1 ([G1] PH0); also elsewhere on the board
16MHZ_OUT: U1.H1 ([H1] PH1); also elsewhere on the board
32KHZ_IN: U1.E1 (PC14 [E1]); also elsewhere on the board
32KHZ_OUT: U1.F1 (PC15 [F1]); also elsewhere on the board
ADC1_3V3: U1.M5 (PC3 [M5]); also elsewhere on the board
ADC1_6V6: U1.M4 (PC2 [M4]); also elsewhere on the board
BOOT0: U1.D6 (BOOT0 [D6]); also elsewhere on the board
BUZZER_1: U1.L2 ([L2] PF9); also elsewhere on the board
CAN1_RX: U1.B12 (PD0 [B12]); also elsewhere on the board
CAN1_TX: U1.C12 (PD1 [C12]); also elsewhere on the board
CAN2_RX: U1.P12 (PB12 [P12]); also elsewhere on the board
CAN2_TX: U1.P13 (PB13 [P13]); also elsewhere on the board
ETH_CRS_DV: U1.R3 (PA7 [R3]); also elsewhere on the board
ETH_MDC: U1.M3 (PC1 [M3]); also elsewhere on the board
ETH_MDIO: U1.P2 (PA2 [P2]); also elsewhere on the board
ETH_POWER_EN: U1.B7 ([B7] PG15); also elsewhere on the board
ETH_REF_CLK: U1.N2 (PA1 [N2]); also elsewhere on the board
ETH_RXD0: U1.N5 (PC4 [N5]); also elsewhere on the board
ETH_RXD1: U1.P5 (PC5 [P5]); also elsewhere on the board
ETH_TXD0: U1.A8 ([A8] PG13); also elsewhere on the board
ETH_TXD1: U1.B8 ([B8] PG12); also elsewhere on the board
ETH_TX_EN: U1.R13 (PB11 [R13]); also elsewhere on the board
FMU_CAP1: U1.P10 ([P10] PE11); also elsewhere on the board
FMU_CH1: U1.E14 ([E14] PI0); also elsewhere on the board
FMU_CH2: U1.K12 ([K12] PH12); also elsewhere on the board
FMU_CH3: U1.L12 ([L12] PH11); also elsewhere on the board
FMU_CH4: U1.L13 ([L13] PH10); also elsewhere on the board
FMU_CH5: U1.M15 (PD13 [M15]); also elsewhere on the board
FMU_CH6: U1.M14 (PD14 [M14]); also elsewhere on the board
FMU_CH7: U1.M11 ([M11] PH6); also elsewhere on the board
FMU_CH8: U1.M13 ([M13] PH9); also elsewhere on the board
FMU_PPM_INPUT: U1.C4 ([C4] PI5); also elsewhere on the board
FMU_SAFETY_SWITCH_IN: U1.K3 ([K3] PF5); also elsewhere on the board
FMU_SWCLK: U1.A14 (PA14 [A14]); also elsewhere on the board
FMU_SWDIO: U1.A15 (PA13 [A15]); also elsewhere on the board
FMU_VDD_3V3: U1.C5 (VDD [C5]), U1.C6 (PDR_ON [C6]), U1.C7 (VDD [C7]), U1.C8 (VDD [C8]), U1.C9 (VDD [C9]), U1.F3 (VDD [F3]), U1.G3 (VDD [G3]), U1.G13 (VDD [G13]), U1.H13 (VDD33_USB [H13]), U1.J12 (VDD [J12]), U1.J13 (VDD [J13]), U1.K4 (VDD [K4]), U1.N8 (VDD [N8]), U1.N9 (VDD [N9]), U1.N10 (VDD [N10]), U1.P1 (VREF+ [P1]), U1.R1 (VDDA [R1]); also elsewhere on the board
FMU_nRST: U1.J1 (NRST [J1]); also elsewhere on the board
FMU_nSAFETY_SWITCH_LED_OUT: U1.N15 (PD10 [N15]); also elsewhere on the board
GND: U1.D5 (VSS [D5]), U1.D7 (VSS [D7]), U1.D8 (VSS [D8]), U1.D9 (VSS [D9]), U1.F2 (VSS [F2]), U1.F6 (VSS [F6]), U1.F7 (VSS [F7]), U1.F8 (VSS [F8]), U1.F9 (VSS [F9]), U1.F10 (VSS [F10]), U1.F12 (VSS [F12]), U1.G2 (VSS [G2]), U1.G6 (VSS [G6]), U1.G7 (VSS [G7]), U1.G8 (VSS [G8]), U1.G9 (VSS [G9]), U1.G10 (VSS [G10]), U1.G12 (VSS [G12]), U1.H6 (VSS [H6]), U1.H7 (VSS [H7]), U1.H8 (VSS [H8]), U1.H9 (VSS [H9]), U1.H10 (VSS [H10]), U1.H12 (VSS [H12]), U1.J6 (VSS [J6]), U1.J7 (VSS [J7]), U1.J8 (VSS [J8]), U1.J9 (VSS [J9]), U1.J10 (VSS [J10]), U1.K6 (VSS [K6]), U1.K7 (VSS [K7]), U1.K8 (VSS [K8]), U1.K9 (VSS [K9]), U1.K10 (VSS [K10]), U1.L4 (VSS [L4]), U1.M1 (VSSA [M1]), U1.M8 (VSS [M8]), U1.M9 (VSS [M9]), U1.N1 (VREF- [N1]); also elsewhere on the board
HEATER: U1.R12 (PB10 [R12]); also elsewhere on the board
HW_REV_SENSE: U1.H4 ([H4] PH4); also elsewhere on the board
HW_VER_REV_DRIVE: U1.N7 ([N7] PG0); also elsewhere on the board
HW_VER_SENSE: U1.G4 ([G4] PH3); also elsewhere on the board
I2C1_SCL_BASE: U1.A5 (PB8 [A5]); also elsewhere on the board
I2C1_SDA_BASE: U1.B4 (PB9 [B4]); also elsewhere on the board
I2C2_DRDY1_BARO2: U1.K13 ([K13] PG5); also elsewhere on the board
I2C2_SCL_BASE: U1.H3 ([H3] PF1); also elsewhere on the board
I2C2_SDA_BASE: U1.E2 ([E2] PF0); also elsewhere on the board
I2C3_SCL_BASE: U1.F15 (PA8 [F15]); also elsewhere on the board
I2C3_SDA_BASE: U1.M12 ([M12] PH8); also elsewhere on the board
I2C4_SCL_FMU: U1.R7 ([R7] PF14); also elsewhere on the board
I2C4_SDA_FMU: U1.P7 ([P7] PF15); also elsewhere on the board
NFC_GPIO: U1.M2 (PC0 [M2]); also elsewhere on the board
PG6: U1.J15 ([J15] PG6); also elsewhere on the board
SCALED_V5: U1.R4 (PB1 [R4]); also elsewhere on the board
SCALED_VDD_3V3_SENSORS1: U1.N3 (PA0 [N3]); also elsewhere on the board
SCALED_VDD_3V3_SENSORS2: U1.N4 (PA4 [N4]); also elsewhere on the board
SCALED_VDD_3V3_SENSORS3: U1.R5 (PB0 [R5]); also elsewhere on the board
SCALED_VDD_3V3_SENSORS4: U1.P6 ([P6] PF12); also elsewhere on the board
SD_CLK: U1.B11 (PD6 [B11]); also elsewhere on the board
SD_CMD: U1.A11 (PD7 [A11]); also elsewhere on the board
SD_D0: U1.R14 (PB14 [R14]); also elsewhere on the board
SD_D1: U1.R15 (PB15 [R15]); also elsewhere on the board
SD_D2: U1.B9 ([B9] PG11); also elsewhere on the board
SD_D3: U1.A9 (PB4 [A9]); also elsewhere on the board
SPI1_DRDY1_IMU3_INT1: U1.H2 ([H2] PF2); also elsewhere on the board
SPI1_MISO_SENSOR1: U1.C10 ([C10] PG9); also elsewhere on the board
SPI1_MOSI_SENSOR1: U1.A6 (PB5 [A6]); also elsewhere on the board
SPI1_SCK_SENSOR1: U1.P4 (PA5 [P4]); also elsewhere on the board
SPI1_nCS1_IMU3: U1.D3 ([D3] PI9); also elsewhere on the board
SPI2_DRDY2_IMU2_INT2: U1.D15 (PA10 [D15]); also elsewhere on the board
SPI2_MISO_SENSOR2: U1.C14 ([C14] PI2); also elsewhere on the board
SPI2_MOSI_SENSOR2: U1.C13 ([C13] PI3); also elsewhere on the board
SPI2_SCK_SENSOR2: U1.D14 ([D14] PI1); also elsewhere on the board
SPI2_nCS1_IMU2: U1.J4 ([J4] PH5); also elsewhere on the board
SPI3_DRDY2_BMI088_INT3_GYRO: U1.C2 ([C2] PI7); also elsewhere on the board
SPI3_MISO_SENSOR3: U1.B13 (PC11 [B13]); also elsewhere on the board
SPI3_MOSI_SENSOR3: U1.M6 (PB2 [M6]); also elsewhere on the board
SPI3_SCK_SENSOR3: U1.B14 (PC10 [B14]); also elsewhere on the board
SPI3_nCS1_BMI088_ACCEL: U1.D4 ([D4] PI4); also elsewhere on the board
SPI3_nCS2_BMI088_GYRO: U1.D2 ([D2] PI8); also elsewhere on the board
SPI5_MISO_FRAM: U1.N12 ([N12] PH7); also elsewhere on the board
SPI5_MOSI_FRAM: U1.R6 ([R6] PF11); also elsewhere on the board
SPI5_SCK_FRAM: U1.K1 ([K1] PF7); also elsewhere on the board
SPI5_nCS1_FRAM: U1.J14 ([J14] PG7); also elsewhere on the board
SPI6_DRDY1_EXTERNAL1: U1.N14 (PD11 [N14]); also elsewhere on the board
SPI6_DRDY2_EXTERNAL1: U1.N13 (PD12 [N13]); also elsewhere on the board
SPI6_MISO_EXTERNAL1: U1.P3 (PA6 [P3]); also elsewhere on the board
SPI6_MOSI_EXTERNAL1: U1.A7 ([A7] PG14); also elsewhere on the board
SPI6_SCK_EXTERNAL1: U1.A10 (PB3 [A10]); also elsewhere on the board
SPI6_nCS1_EXTERNAL1: U1.E3 ([E3] PI10); also elsewhere on the board
SPI6_nCS2_EXTERNAL1: U1.A13 (PA15 [A13]); also elsewhere on the board
SPI6_nRESET_EXTERNAL1: U1.L1 ([L1] PF10); also elsewhere on the board
SPIX_SYNC: U1.P9 ([P9] PE9); also elsewhere on the board
TRACECLK: U1.A2 ([A2] PE2); also elsewhere on the board
UART4_RX: U1.E13 ([E13] PH14); also elsewhere on the board
UART4_TX: U1.E12 ([E12] PH13); also elsewhere on the board
UART5_CTS_TELEM2: U1.F14 (PC9 [F14]); also elsewhere on the board
UART5_RTS_TELEM2: U1.G14 (PC8 [G14]); also elsewhere on the board
UART5_RX_TELEM2: U1.D12 (PD2 [D12]); also elsewhere on the board
UART5_TX_TELEM2: U1.A12 (PC12 [A12]); also elsewhere on the board
UART7_CTS_TELEM1: U1.R9 ([R9] PE10); also elsewhere on the board
UART7_RTS_TELEM1: U1.L3 ([L3] PF8); also elsewhere on the board
UART7_RX_TELEM1: U1.K2 ([K2] PF6); also elsewhere on the board
UART7_TX_TELEM1: U1.P8 ([P8] PE8); also elsewhere on the board
UART8_RX_GPS2: U1.A4 ([A4] PE0); also elsewhere on the board
UART8_TX_GPS2: U1.A3 ([A3] PE1); also elsewhere on the board
USART1_RX_GPS1: U1.B5 (PB7 [B5]); also elsewhere on the board
USART1_TX_GPS1: U1.B6 (PB6 [B6]); also elsewhere on the board
USART2_CTS_TELEM3: U1.D11 (PD3 [D11]); also elsewhere on the board
USART2_RTS_TELEM3: U1.D10 (PD4 [D10]); also elsewhere on the board
USART2_RX_TELEM3: U1.R2 (PA3 [R2]); also elsewhere on the board
USART2_TX_TELEM3: U1.C11 (PD5 [C11]); also elsewhere on the board
USART3_RX_DEBUG: U1.P14 (PD9 [P14]); also elsewhere on the board
USART3_TX_DEBUG: U1.P15 (PD8 [P15]); also elsewhere on the board
USART6_RX_FROM_IO_RC: U1.G15 (PC7 [G15]); also elsewhere on the board
USART6_TX_TO_IO: U1.H15 (PC6 [H15]); also elsewhere on the board
USB_D_N: U1.C15 (PA11 [C15]); also elsewhere on the board
USB_D_P: U1.B15 (PA12 [B15]); also elsewhere on the board
VBUS_SENSE: U1.E15 (PA9 [E15]); also elsewhere on the board
VCAP: U1.F13 (VCAP [F13]), U1.M10 (VCAP [M10]); also elsewhere on the board
VDD_3V3_SD_CARD_EN: U1.D1 (PC13 [D1]); also elsewhere on the board
VDD_3V3_SENSORS1_EN: U1.E4 ([E4] PI11); also elsewhere on the board
VDD_3V3_SENSORS2_EN: U1.J3 ([J3] PF4); also elsewhere on the board
VDD_3V3_SENSORS3_EN: U1.R8 ([R8] PE7); also elsewhere on the board
VDD_3V3_SENSORS4_EN: U1.H14 ([H14] PG8); also elsewhere on the board
VDD_3V3_SPEKTRUM_POWER_EN: U1.F4 ([F4] PH2); also elsewhere on the board
VDD_5V_HIPOWER_nEN: U1.B10 ([B10] PG10); also elsewhere on the board
VDD_5V_HIPOWER_nOC: U1.N6 ([N6] PF13); also elsewhere on the board
VDD_5V_PERIPH_nEN: U1.K14 ([K14] PG4); also elsewhere on the board
VDD_5V_PERIPH_nOC: U1.R11 ([R11] PE15); also elsewhere on the board
V_RTC_BAT: U1.C1 (VBAT [C1]); also elsewhere on the board
nARMED: U1.B3 ([B3] PE6); also elsewhere on the board
nLED_BLUE: U1.B2 ([B2] PE5); also elsewhere on the board
nLED_GREEN: U1.B1 ([B1] PE4); also elsewhere on the board
nLED_RED: U1.A1 ([A1] PE3); also elsewhere on the board
nPOWER_IN_A: U1.M7 ([M7] PG1); also elsewhere on the board
nPOWER_IN_B: U1.L15 ([L15] PG2); also elsewhere on the board
nPOWER_IN_C: U1.K15 ([K15] PG3); also elsewhere on the board

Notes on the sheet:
U1 STM32H743IIK6, UFBGA176+25. Only connected balls are drawn; pin numbers are the ball names from ST's pin data. Unused GPIO balls are left open on the PCB.
